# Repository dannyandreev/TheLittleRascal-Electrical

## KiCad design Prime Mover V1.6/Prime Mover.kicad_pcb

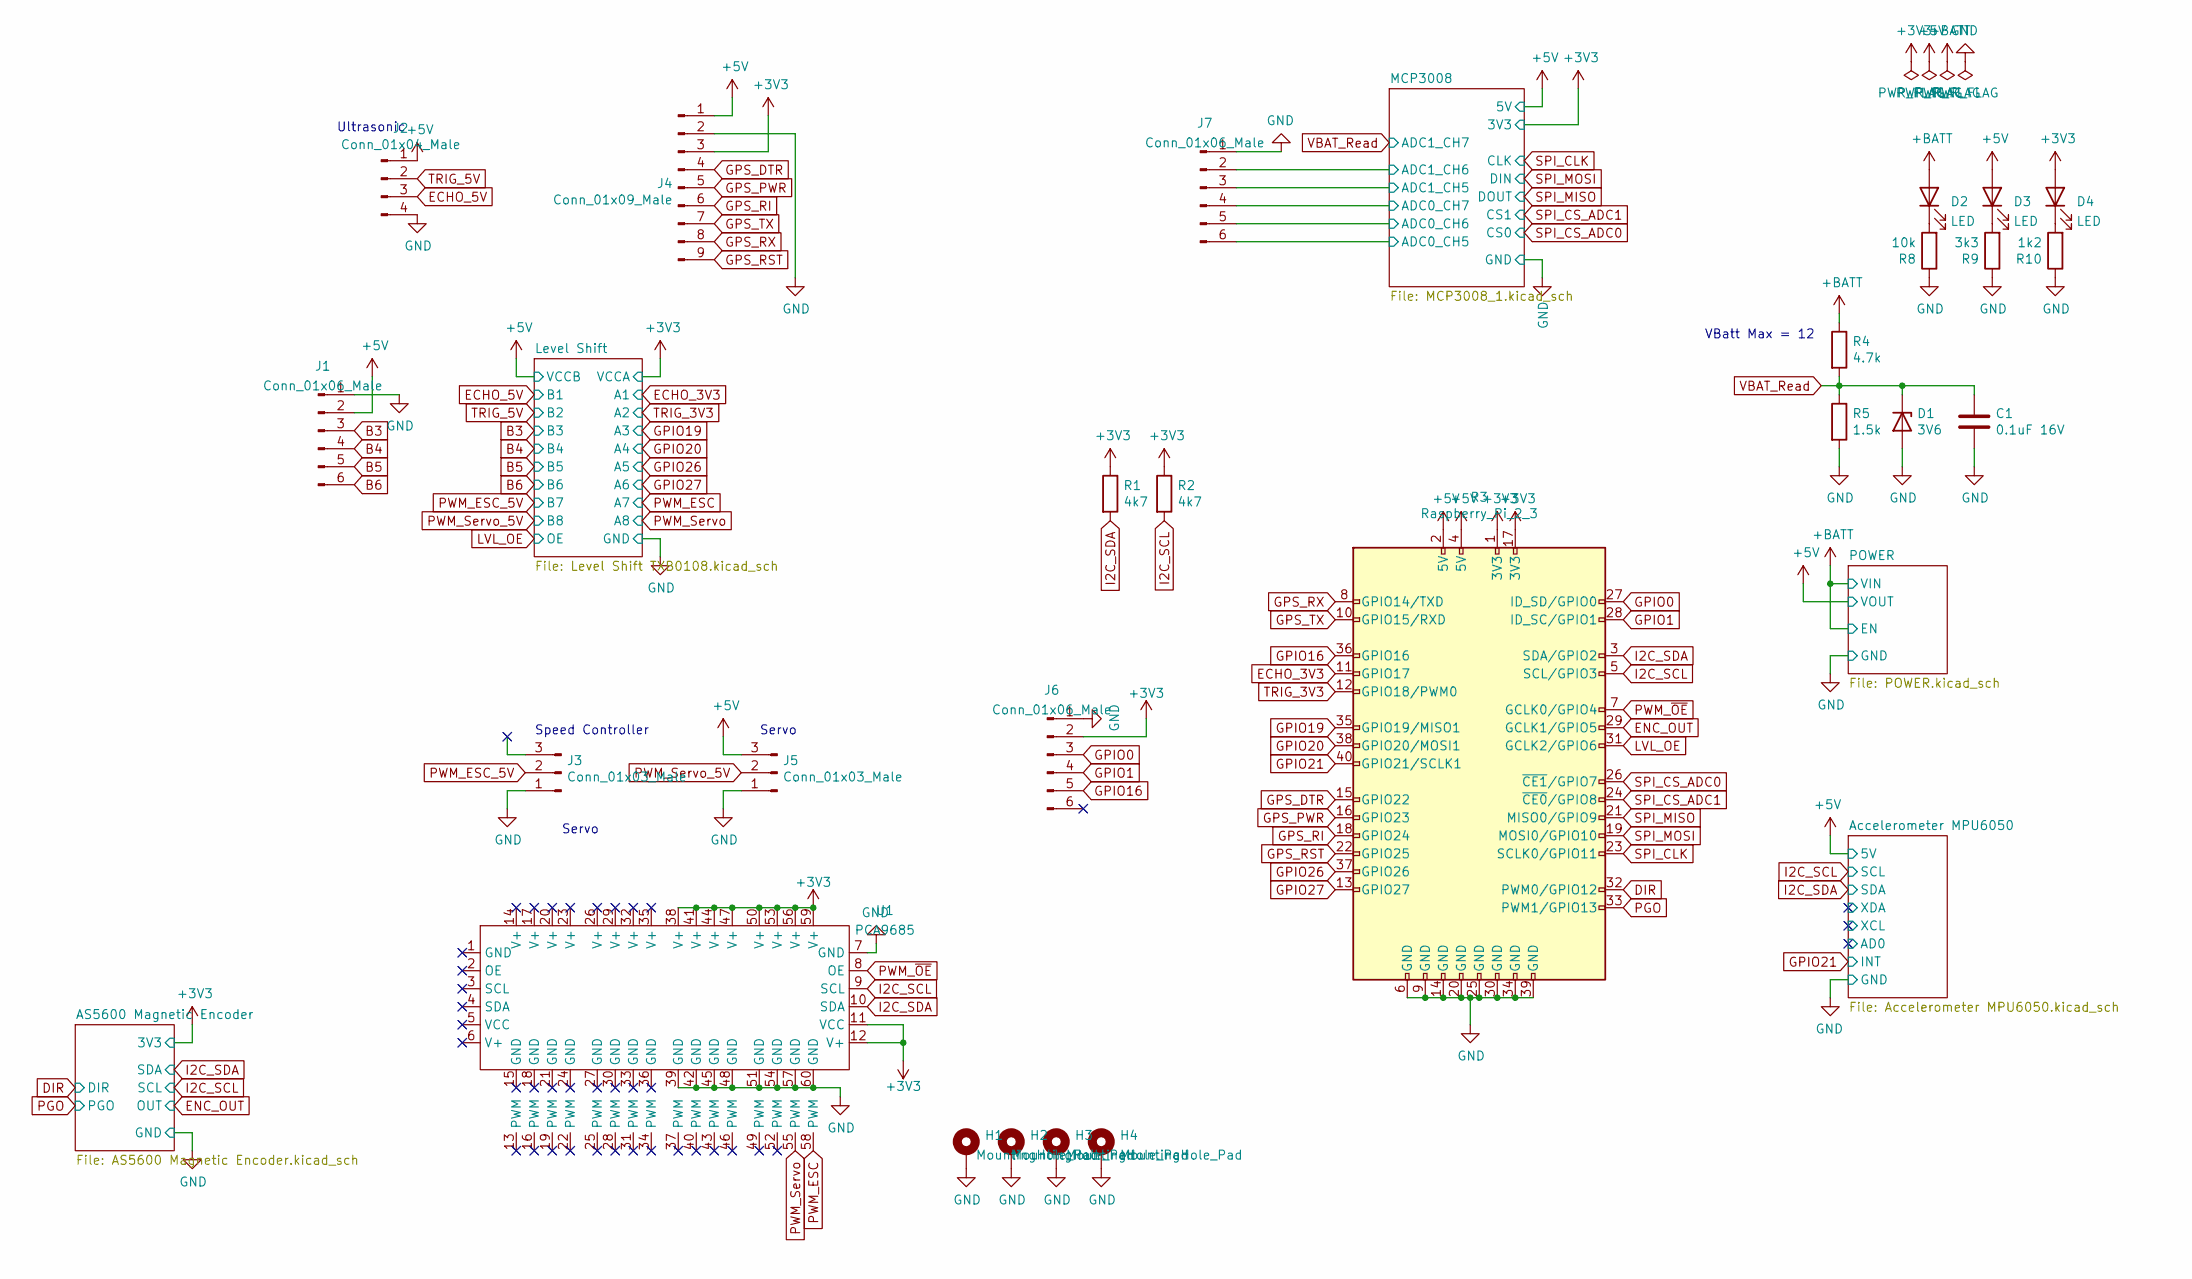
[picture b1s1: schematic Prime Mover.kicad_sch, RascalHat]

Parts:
C1: 0.1uF 16V; C_0805_2012Metric
D1: 3V6; D_SOD-323_HandSoldering
D2, D3, D4: LED; LED_0805_2012Metric
H1, H2, H3, H4: MountingHole_Pad; MountingHole_3.2mm_M3_DIN965_Pad
J1, J6, J7: Conn_01x06_Male; JST_PH_B6B-PH-K_1x06_P2.00mm_Vertical
J2: Conn_01x04_Male; JST_PH_B4B-PH-K_1x04_P2.00mm_Vertical
J3, J5: Conn_01x03_Male; JST_PH_B3B-PH-K_1x03_P2.00mm_Vertical
J4: Conn_01x09_Male; JST_PH_B9B-PH-K_1x09_P2.00mm_Vertical
R1, R2: 4k7; R_0805_2012Metric
R3: Raspberry_Pi_2_3; PinSocket_2x20_P2.54mm_Vertical
R4: 4.7k; R_0805_2012Metric
R5: 1.5k; R_0805_2012Metric
R8: 10k; R_0805_2012Metric
R9: 3k3; R_0805_2012Metric
R10: 1k2; R_0805_2012Metric
U1: PCA9685; PCA9685 HW170

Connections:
+3V3: D4.2 (A), J4.3, J6.2, R1.1, R2.1, R3.1 (3V3), R3.17 (3V3), U1.11 (VCC), U1.12 (V+), U1.38 (V+), U1.41 (V+), U1.44 (V+), U1.47 (V+), U1.50 (V+), U1.53 (V+), U1.56 (V+), U1.59 (V+); also elsewhere on the board
+5V: D3.2 (A), J1.2, J2.1, J4.1, J5.3, R3.2 (5V), R3.4 (5V); also elsewhere on the board
+BATT: D2.2 (A), R4.1; also elsewhere on the board
/MCP3008/ADC0_CH5: J7.6; also elsewhere on the board
/MCP3008/ADC0_CH6: J7.5; also elsewhere on the board
/MCP3008/ADC0_CH7: J7.4; also elsewhere on the board
/MCP3008/ADC1_CH5: J7.3; also elsewhere on the board
/MCP3008/ADC1_CH6: J7.2; also elsewhere on the board
B3: J1.3; also elsewhere on the board
B4: J1.4; also elsewhere on the board
B5: J1.5; also elsewhere on the board
B6: J1.6; also elsewhere on the board
DIR: R3.32 (PWM0/GPIO12); also elsewhere on the board
ECHO_3V3: R3.11 (GPIO17); also elsewhere on the board
ECHO_5V: J2.3; also elsewhere on the board
ENC_OUT: R3.29 (GCLK1/GPIO5); also elsewhere on the board
GND: C1.2, D1.2 (A), H1.1, H2.1, H3.1, H4.1, J1.1, J2.4, J3.1, J4.2, J5.1, J6.1, J7.1, R3.6 (GND), R3.9 (GND), R3.14 (GND), R3.20 (GND), R3.25 (GND), R3.30 (GND), R3.34 (GND), R3.39 (GND), R5.2, R8.1, R9.1, R10.1, U1.7 (GND), U1.39 (GND), U1.42 (GND), U1.45 (GND), U1.48 (GND), U1.51 (GND), U1.54 (GND), U1.57 (GND), U1.60 (GND); also elsewhere on the board
GPIO0: J6.3, R3.27 (ID_SD/GPIO0)
GPIO1: J6.4, R3.28 (ID_SC/GPIO1)
GPIO16: J6.5, R3.36 (GPIO16)
GPIO19: R3.35 (GPIO19/MISO1); also elsewhere on the board
GPIO20: R3.38 (GPIO20/MOSI1); also elsewhere on the board
GPIO21: R3.40 (GPIO21/SCLK1); also elsewhere on the board
GPIO26: R3.37 (GPIO26); also elsewhere on the board
GPIO27: R3.13 (GPIO27); also elsewhere on the board
GPS_DTR: J4.4, R3.15 (GPIO22)
GPS_PWR: J4.5, R3.16 (GPIO23)
GPS_RI: J4.6, R3.18 (GPIO24)
GPS_RST: J4.9, R3.22 (GPIO25)
GPS_RX: J4.8, R3.8 (GPIO14/TXD)
GPS_TX: J4.7, R3.10 (GPIO15/RXD)
I2C_SCL: R2.2, R3.5 (SCL/GPIO3), U1.9 (SCL); also elsewhere on the board
I2C_SDA: R1.2, R3.3 (SDA/GPIO2), U1.10 (SDA); also elsewhere on the board
LVL_OE: R3.31 (GCLK2/GPIO6); also elsewhere on the board
unnamed: D2.1 (K), R8.2
unnamed: D3.1 (K), R9.2
unnamed: D4.1 (K), R10.2
PGO: R3.33 (PWM1/GPIO13); also elsewhere on the board
PWM_ESC: U1.58 (PWM); also elsewhere on the board
PWM_ESC_5V: J3.2; also elsewhere on the board
PWM_Servo: U1.55 (PWM); also elsewhere on the board
PWM_Servo_5V: J5.2; also elsewhere on the board
PWM_~OE: R3.7 (GCLK0/GPIO4), U1.8 (OE)
SPI_CLK: R3.23 (SCLK0/GPIO11); also elsewhere on the board
SPI_CS_ADC0: R3.26 (~CE1/GPIO7); also elsewhere on the board
SPI_CS_ADC1: R3.24 (~CE0/GPIO8); also elsewhere on the board
SPI_MISO: R3.21 (MISO0/GPIO9); also elsewhere on the board
SPI_MOSI: R3.19 (MOSI0/GPIO10); also elsewhere on the board
TRIG_3V3: R3.12 (GPIO18/PWM0); also elsewhere on the board
TRIG_5V: J2.2; also elsewhere on the board
VBAT_Read: C1.1, D1.1 (K), R4.2, R5.1; also elsewhere on the board

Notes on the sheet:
Servo
VBatt Max = 12
Ultrasonic
Speed Controller

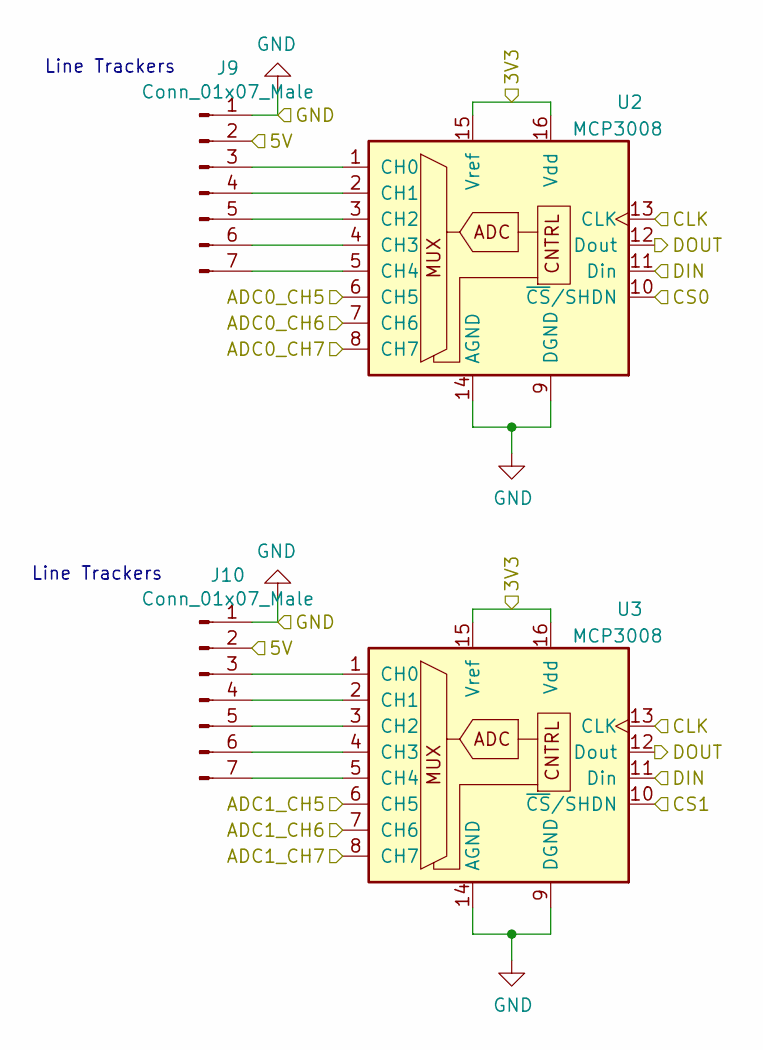
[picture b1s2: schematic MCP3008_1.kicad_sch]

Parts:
J9, J10: Conn_01x07_Male; JST_PH_B7B-PH-K_1x07_P2.00mm_Vertical
U2, U3: MCP3008; SOIC-16_3.9x9.9mm_P1.27mm

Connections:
+3V3: U2.15 (Vref), U2.16 (Vdd), U3.15 (Vref), U3.16 (Vdd); also elsewhere on the board
+5V: J9.2, J10.2; also elsewhere on the board
/MCP3008/ADC0_CH5: U2.6 (CH5); also elsewhere on the board
/MCP3008/ADC0_CH6: U2.7 (CH6); also elsewhere on the board
/MCP3008/ADC0_CH7: U2.8 (CH7); also elsewhere on the board
/MCP3008/ADC1_CH5: U3.6 (CH5); also elsewhere on the board
/MCP3008/ADC1_CH6: U3.7 (CH6); also elsewhere on the board
GND: J9.1, J10.1, U2.9 (DGND), U2.14 (AGND), U3.9 (DGND), U3.14 (AGND); also elsewhere on the board
unnamed: J9.3, U2.1 (CH0)
unnamed: J9.4, U2.2 (CH1)
unnamed: J9.5, U2.3 (CH2)
unnamed: J9.6, U2.4 (CH3)
unnamed: J9.7, U2.5 (CH4)
unnamed: J10.3, U3.1 (CH0)
unnamed: J10.4, U3.2 (CH1)
unnamed: J10.5, U3.3 (CH2)
unnamed: J10.6, U3.4 (CH3)
unnamed: J10.7, U3.5 (CH4)
SPI_CLK: U2.13 (CLK), U3.13 (CLK); also elsewhere on the board
SPI_CS_ADC0: U2.10 (~CS/SHDN); also elsewhere on the board
SPI_CS_ADC1: U3.10 (~CS/SHDN); also elsewhere on the board
SPI_MISO: U2.12 (Dout), U3.12 (Dout); also elsewhere on the board
SPI_MOSI: U2.11 (Din), U3.11 (Din); also elsewhere on the board
VBAT_Read: U3.8 (CH7); also elsewhere on the board

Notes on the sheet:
Line Trackers

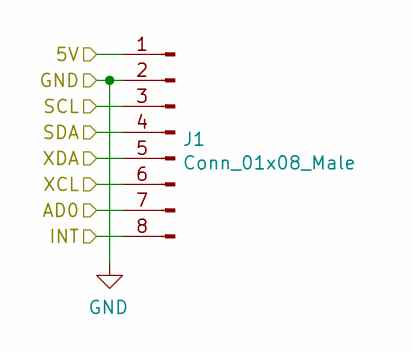
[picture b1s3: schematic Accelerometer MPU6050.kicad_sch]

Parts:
J1: Conn_01x08_Male; MPU-6050-Module

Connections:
+5V: J1.2; also elsewhere on the board
B3: J1.3; also elsewhere on the board
B4: J1.4; also elsewhere on the board
B5: J1.5; also elsewhere on the board
B6: J1.6; also elsewhere on the board
GND: J1.1; also elsewhere on the board

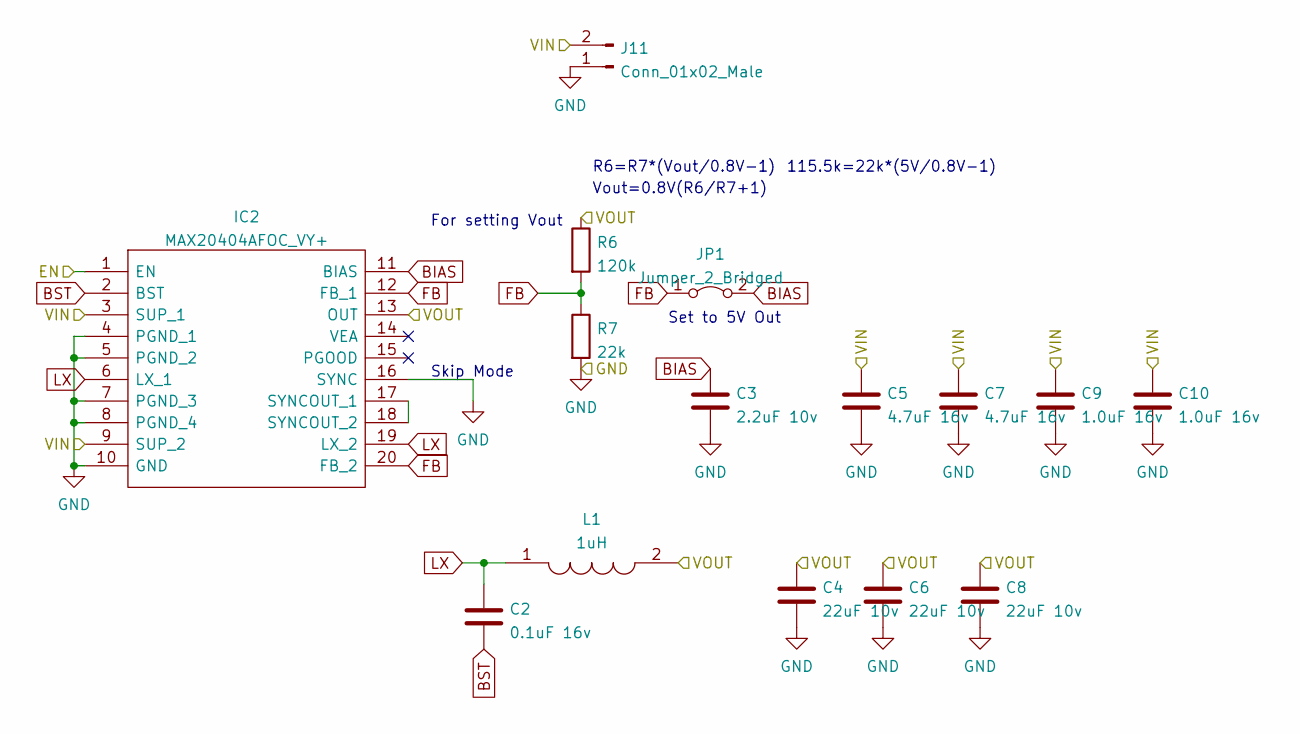
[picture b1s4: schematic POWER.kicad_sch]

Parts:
C2: 0.1uF 16v; C_0805_2012Metric
C3: 2.2uF 10v; C_0805_2012Metric
C4, C6, C8: 22uF 10v; CP_Elec_5x5.3
C5, C7: 4.7uF 16v; C_0805_2012Metric
C9, C10: 1.0uF 16v; C_0805_2012Metric
IC2: MAX20404AFOC_VY+; MAX20404AFOCVY; Manufacturer_Part_Number MAX20404AFOC/VY+
J11: Conn_01x02_Male; AMASS_XT60-M_1x02_P7.20mm_Vertical
JP1: Jumper_2_Bridged; SolderJumper-2_P1.3mm_Open_RoundedPad1.0x1.5mm
L1: 1uH; INDPM7066X500N; Manufacturer_Part_Number MWSA0605S-150MT
R6: 120k; R_0805_2012Metric
R7: 22k; R_0805_2012Metric

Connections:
+5V: C4.1, C6.1, C8.1, IC2.13 (OUT), L1.2, R6.1; also elsewhere on the board
+BATT: C5.1, C7.1, C9.1, C10.1, IC2.1 (EN), IC2.3 (SUP_1), IC2.9 (SUP_2), J11.2; also elsewhere on the board
BIAS: C3.1, IC2.11 (BIAS), JP1.2 (B)
BST: C2.2, IC2.2 (BST)
FB: IC2.12 (FB_1), IC2.20 (FB_2), JP1.1 (A), R6.2, R7.1
GND: C3.2, C4.2, C5.2, C6.2, C7.2, C8.2, C9.2, C10.2, IC2.4 (PGND_1), IC2.5 (PGND_2), IC2.7 (PGND_3), IC2.8 (PGND_4), IC2.10 (GND), IC2.16 (SYNC), J11.1, R7.2; also elsewhere on the board
LX: C2.1, IC2.6 (LX_1), IC2.19 (LX_2), L1.1
unnamed: IC2.17 (SYNCOUT_1), IC2.18 (SYNCOUT_2)

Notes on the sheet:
Vout=0.8V(R6/R7+1)
For setting Vout
Skip Mode
Set to 5V Out
R6=R7*(Vout/0.8V-1)
115.5k=22k*(5V/0.8V-1)

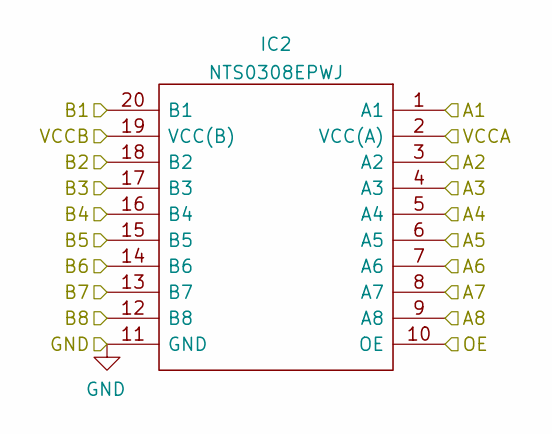
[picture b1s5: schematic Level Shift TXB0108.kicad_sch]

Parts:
IC2: NTS0308EPWJ; SOP65P640X110-20N; Manufacturer_Part_Number NTS0308EPWJ; Mouser Part Number 771-NTS0308EPWJ

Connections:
+5V: IC2.13 (OUT); also elsewhere on the board
+BATT: IC2.1 (EN), IC2.3 (SUP_1), IC2.9 (SUP_2); also elsewhere on the board
BIAS: IC2.11 (BIAS); also elsewhere on the board
BST: IC2.2 (BST); also elsewhere on the board
FB: IC2.12 (FB_1), IC2.20 (FB_2); also elsewhere on the board
GND: IC2.4 (PGND_1), IC2.5 (PGND_2), IC2.7 (PGND_3), IC2.8 (PGND_4), IC2.10 (GND), IC2.16 (SYNC); also elsewhere on the board
LX: IC2.6 (LX_1), IC2.19 (LX_2); also elsewhere on the board
unnamed: IC2.17 (SYNCOUT_1), IC2.18 (SYNCOUT_2)

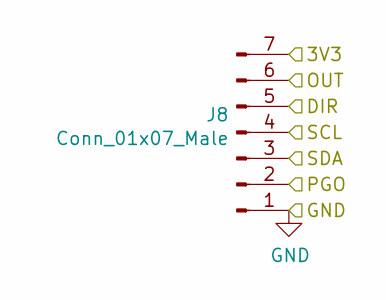
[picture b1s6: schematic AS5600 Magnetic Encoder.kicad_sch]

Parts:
J8: Conn_01x07_Male; JST_PH_B7B-PH-K_1x07_P2.00mm_Vertical

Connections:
+3V3: J8.7; also elsewhere on the board
DIR: J8.5; also elsewhere on the board
ENC_OUT: J8.6; also elsewhere on the board
GND: J8.1; also elsewhere on the board
I2C_SCL: J8.4; also elsewhere on the board
I2C_SDA: J8.3; also elsewhere on the board
PGO: J8.2; also elsewhere on the board

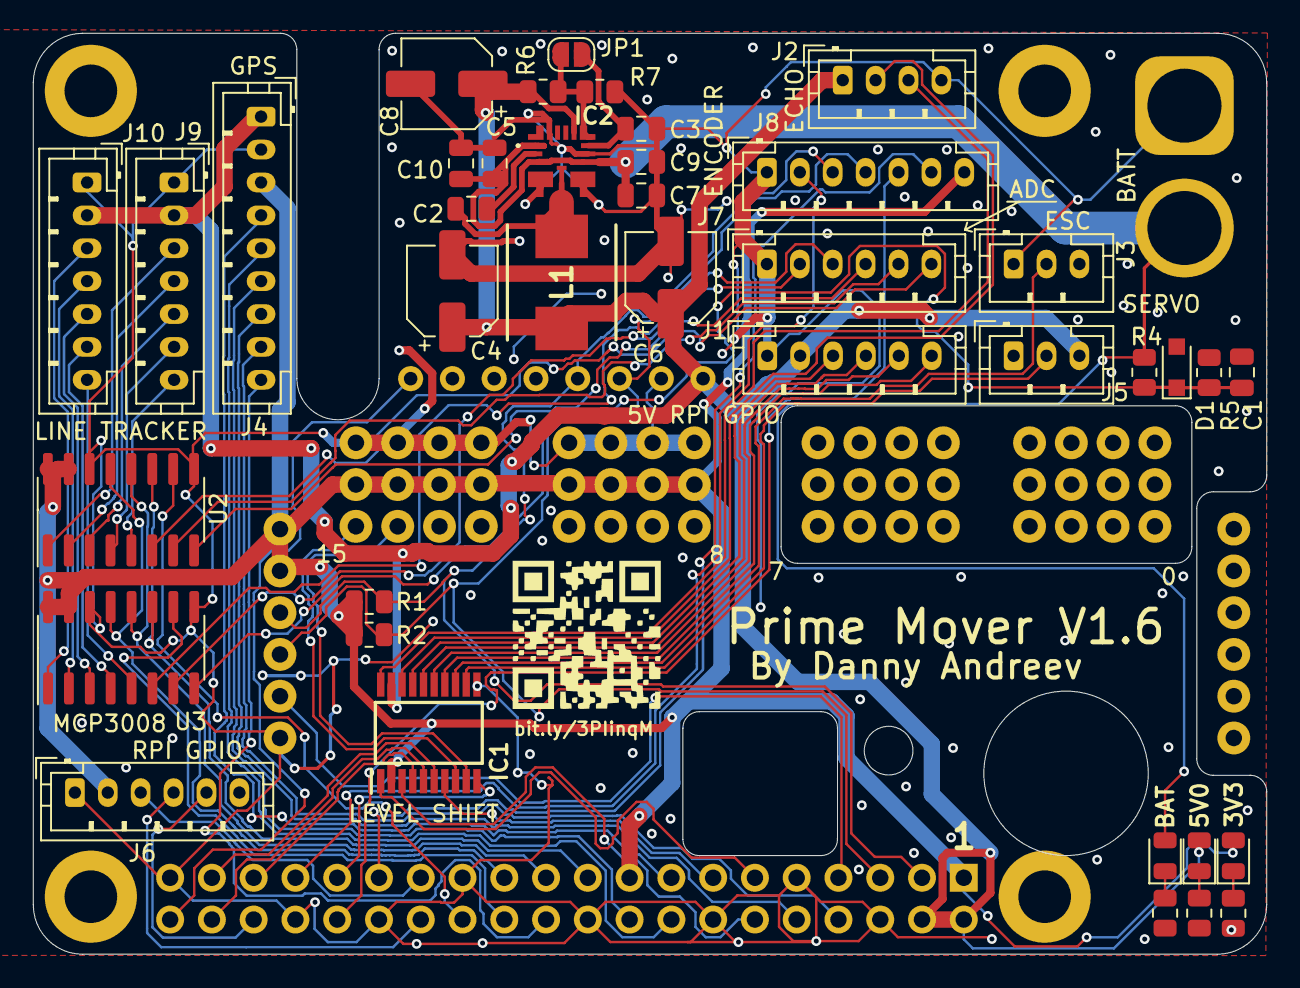
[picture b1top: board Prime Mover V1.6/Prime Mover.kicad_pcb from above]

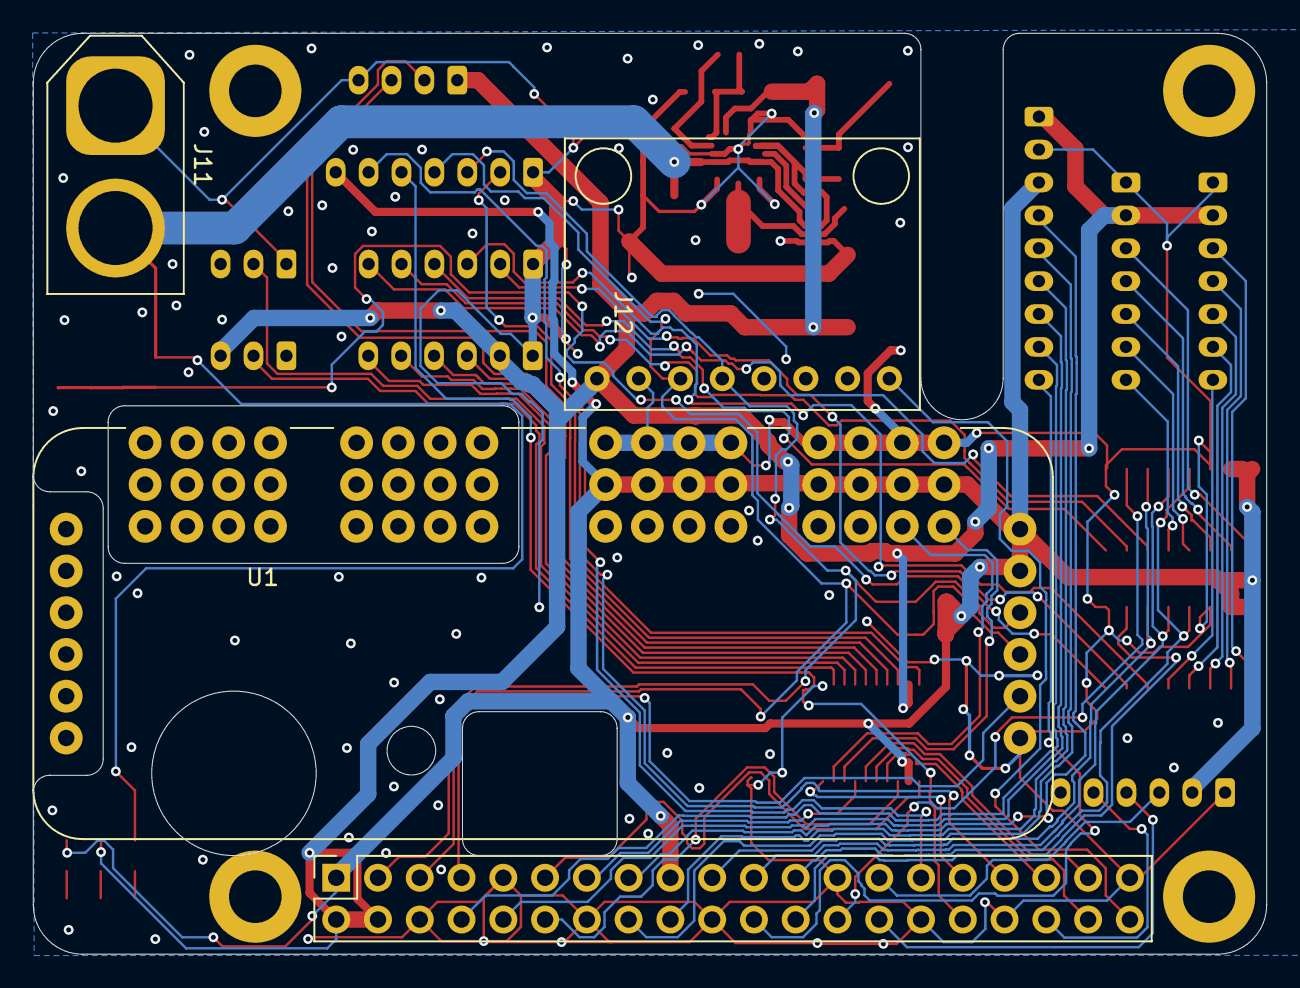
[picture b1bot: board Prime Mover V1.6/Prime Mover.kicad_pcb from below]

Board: 2 copper layers, 75.0 x 56.0 mm, 47 parts (3 on the bottom side), 66 nets.

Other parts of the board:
IC1: NTS0308EPWJ; SOP65P640X110-20N
J12: Conn_01x08_Male; MPU-6050-Module

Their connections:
+3V3: IC1.2 (VCC(A)); also elsewhere on the board
+5V: IC1.19 (VCC(B)), J12.1; also elsewhere on the board
B3: IC1.17 (B3); also elsewhere on the board
B4: IC1.16 (B4); also elsewhere on the board
B5: IC1.15 (B5); also elsewhere on the board
B6: IC1.14 (B6); also elsewhere on the board
ECHO_3V3: IC1.1 (A1); also elsewhere on the board
ECHO_5V: IC1.20 (B1); also elsewhere on the board
GND: IC1.11 (GND), J12.2; also elsewhere on the board
GPIO19: IC1.4 (A3); also elsewhere on the board
GPIO20: IC1.5 (A4); also elsewhere on the board
GPIO21: J12.8; also elsewhere on the board
GPIO26: IC1.6 (A5); also elsewhere on the board
GPIO27: IC1.7 (A6); also elsewhere on the board
I2C_SCL: J12.3; also elsewhere on the board
I2C_SDA: J12.4; also elsewhere on the board
LVL_OE: IC1.10 (OE); also elsewhere on the board
PWM_ESC: IC1.8 (A7); also elsewhere on the board
PWM_ESC_5V: IC1.13 (B7); also elsewhere on the board
PWM_Servo: IC1.9 (A8); also elsewhere on the board
PWM_Servo_5V: IC1.12 (B8); also elsewhere on the board
TRIG_3V3: IC1.3 (A2); also elsewhere on the board
TRIG_5V: IC1.18 (B2); also elsewhere on the board

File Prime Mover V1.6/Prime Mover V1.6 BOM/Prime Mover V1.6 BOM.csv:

Id,Designator,Package,Quantity,Designation,Supplier and ref,
1,JP1,SolderJumper-2_P1.3mm_Open_RoundedPad1.0x1.5mm,1,Jumper_2_Bridged,N/A,
2,"C7,C5",C_0805_2012Metric,2,4.7uF 16v,EMF212AB7475MGHT ,
3,"J7,J6,J1",JST_PH_B6B-PH-K_1x06_P2.00mm_Vertical,3,Conn_01x06_Male,B6B-PH-K-S(LF)(SN) ,
4,"C8,C6,C4",CP_Elec_5x5.3,3,22uF 10v,875105242005,Double Check
5,IC1,SOP65P640X110-20N,1,NTS0308EPWJ,NTS0308EPWJ,
6,"U2,U3",SOIC-16_3.9x9.9mm_P1.27mm,2,MCP3008,MCP3008,
7,"J9,J10,J8",JST_PH_B7B-PH-K_1x07_P2.00mm_Vertical,3,Conn_01x07_Male,B7B-PH-K-S(LF)(SN),
8,"H1,H4,H3,H2",MountingHole_3.2mm_M3_DIN965_Pad,4,MountingHole_Pad,N/A,
9,R8,R_0805_2012Metric,1,10k,RMCF0805JT10K0 ,
10,"D2,D4,D3",LED_0805_2012Metric,3,LED,XZMOK54W-1 ,
11,R6,R_0805_2012Metric,1,120k,RMCF0805JT120K ,
12,L1,INDPM7066X500N,1,1uH,MWSA0624S-1R0MT ,
13,J2,JST_PH_B4B-PH-K_1x04_P2.00mm_Vertical,1,Conn_01x04_Male,B4B-PH-K-S(LF)(SN) ,
14,R7,R_0805_2012Metric,1,22k,ERJ-6GEYJ223V ,
15,"C10,C9",C_0805_2012Metric,2,1.0uF 16v,CC0805MKX7R7BB105 ,
16,J4,JST_PH_B9B-PH-K_1x09_P2.00mm_Vertical,1,Conn_01x09_Male,B9B-PH-K-S(LF)(SN) ,
17,R10,R_0805_2012Metric,1,1k2,RMCF0805JT1K20 ,
18,U1,PCA9685 HW170,0,PCA9685,N/A,
19,"R2,R1",R_0805_2012Metric,2,4k7,RMCF0805JT4K70 ,
20,R4,R_0805_2012Metric,1,4.7k,RMCF0805JT4K70 ,
21,R9,R_0805_2012Metric,1,3k3,RNCF0805DTE3K32 ,
22,"J3,J5",JST_PH_B3B-PH-K_1x03_P2.00mm_Vertical,2,Conn_01x03_Male,B3B-PH-K-S(LF)(SN) ,
23,IC2,MAX20404AFOCVY,1,MAX20404AFOC_VY+,MAX20405AFOD/VY+ ,
24,R5,R_0805_2012Metric,1,1.5k,RNCP0805FTD1K50 ,
25,C1,C_0805_2012Metric,1,0.1uF 16V,0805YC104JAT4A ,
26,D1,D_SOD-323_HandSoldering,1,3V6,BZT52C3V6S-7-F ,
27,C2,C_0805_2012Metric,1,0.1uF 16v,0805YC104JAT4A ,
28,C3,C_0805_2012Metric,1,2.2uF 10v,C0805X225K8RAC7800 ,
29,J11,AMASS_XT60-M_1x02_P7.20mm_Vertical,1,Conn_01x02_Male,AMASS_XT60-M,
30,R3,PinSocket_2x20_P2.54mm_Vertical,1,Raspberry_Pi_2_3,PPTC202LFBN-RC ,
31,J12,MPU-6050-Module,0,Conn_01x08_Male,N/A,

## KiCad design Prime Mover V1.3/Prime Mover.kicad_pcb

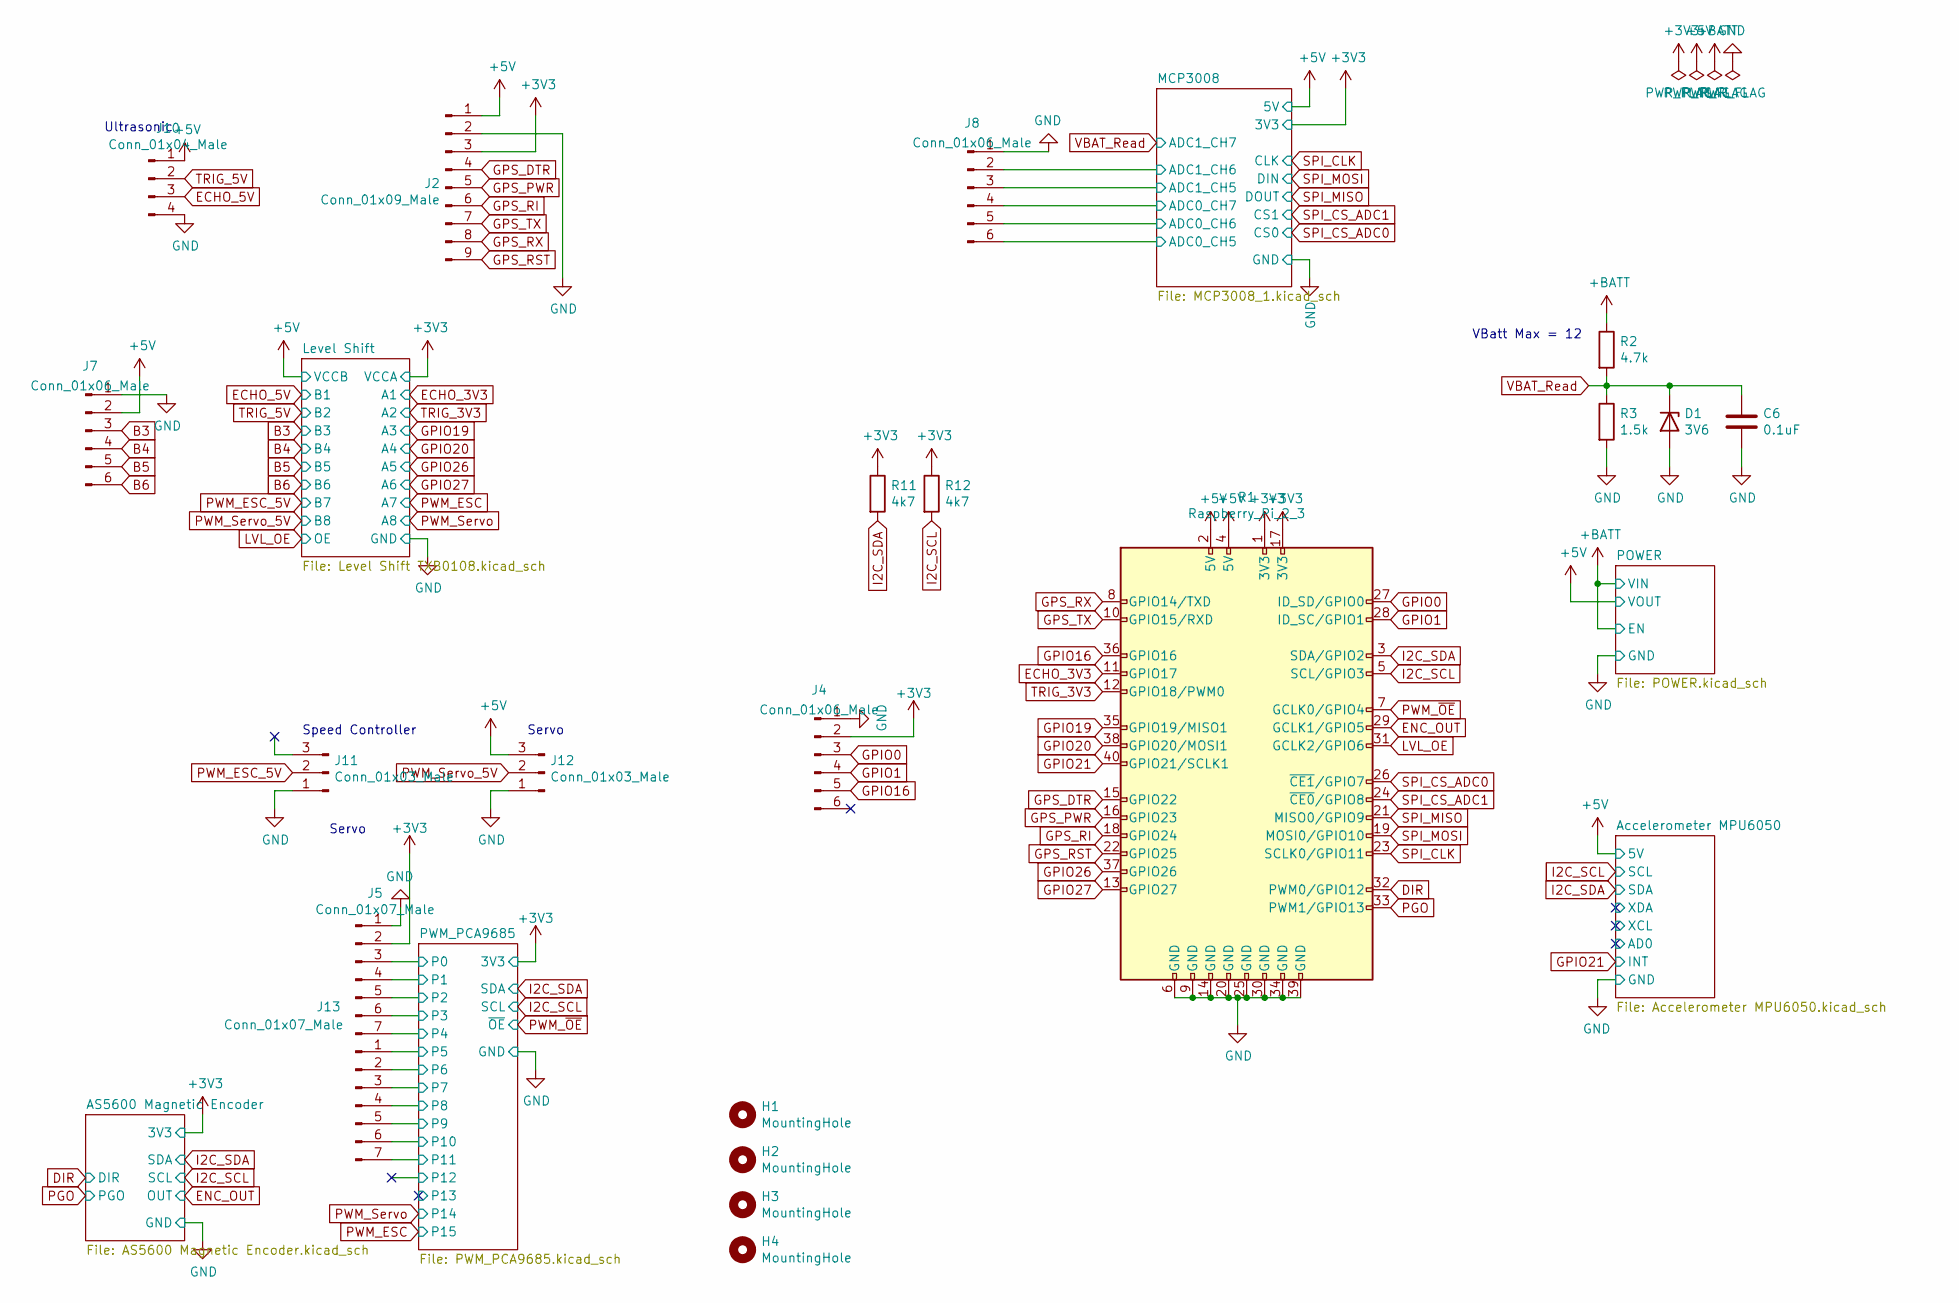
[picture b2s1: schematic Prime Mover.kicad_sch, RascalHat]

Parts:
C6: 0.1uF; C_0805_2012Metric
D1: 3V6; D_SOD-323_HandSoldering
H1, H2, H3, H4: MountingHole; MountingHole_3.2mm_M3
J2: Conn_01x09_Male; JST_PH_B9B-PH-K_1x09_P2.00mm_Vertical
J4, J7, J8: Conn_01x06_Male; JST_PH_B6B-PH-K_1x06_P2.00mm_Vertical
J5, J13: Conn_01x07_Male; JST_PH_B7B-PH-K_1x07_P2.00mm_Vertical
J10: Conn_01x04_Male; JST_PH_B4B-PH-K_1x04_P2.00mm_Vertical
J11, J12: Conn_01x03_Male; JST_PH_B3B-PH-K_1x03_P2.00mm_Vertical
R1: Raspberry_Pi_2_3; PinSocket_2x20_P2.54mm_Vertical
R2: 4.7k; R_0805_2012Metric
R3: 1.5k; R_0805_2012Metric
R11, R12: 4k7; R_0805_2012Metric

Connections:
+3V3: J2.3, J4.2, J5.2, R1.1 (3V3), R1.17 (3V3), R11.1, R12.1; also elsewhere on the board
+5V: J2.1, J7.2, J10.1, J12.3, R1.2 (5V), R1.4 (5V); also elsewhere on the board
+BATT: R2.1; also elsewhere on the board
/MCP3008/ADC0_CH5: J8.6; also elsewhere on the board
/MCP3008/ADC0_CH6: J8.5; also elsewhere on the board
/MCP3008/ADC0_CH7: J8.4; also elsewhere on the board
/MCP3008/ADC1_CH5: J8.3; also elsewhere on the board
/MCP3008/ADC1_CH6: J8.2; also elsewhere on the board
/PWM_PCA9685/P0: J5.3; also elsewhere on the board
/PWM_PCA9685/P1: J5.4; also elsewhere on the board
/PWM_PCA9685/P2: J5.5; also elsewhere on the board
/PWM_PCA9685/P3: J5.6; also elsewhere on the board
/PWM_PCA9685/P4: J5.7; also elsewhere on the board
/PWM_PCA9685/P5: J13.1; also elsewhere on the board
/PWM_PCA9685/P6: J13.2; also elsewhere on the board
/PWM_PCA9685/P7: J13.3; also elsewhere on the board
/PWM_PCA9685/P8: J13.4; also elsewhere on the board
/PWM_PCA9685/P9: J13.5; also elsewhere on the board
/PWM_PCA9685/P10: J13.6; also elsewhere on the board
/PWM_PCA9685/P11: J13.7; also elsewhere on the board
B3: J7.3; also elsewhere on the board
B4: J7.4; also elsewhere on the board
B5: J7.5; also elsewhere on the board
B6: J7.6; also elsewhere on the board
DIR: R1.32 (PWM0/GPIO12); also elsewhere on the board
ECHO_3V3: R1.11 (GPIO17); also elsewhere on the board
ECHO_5V: J10.3; also elsewhere on the board
ENC_OUT: R1.29 (GCLK1/GPIO5); also elsewhere on the board
GND: C6.2, D1.2 (A), J2.2, J4.1, J5.1, J7.1, J8.1, J10.4, J11.1, J12.1, R1.6 (GND), R1.9 (GND), R1.14 (GND), R1.20 (GND), R1.25 (GND), R1.30 (GND), R1.34 (GND), R1.39 (GND), R3.2; also elsewhere on the board
GPIO0: J4.3, R1.27 (ID_SD/GPIO0)
GPIO1: J4.4, R1.28 (ID_SC/GPIO1)
GPIO16: J4.5, R1.36 (GPIO16)
GPIO19: R1.35 (GPIO19/MISO1); also elsewhere on the board
GPIO20: R1.38 (GPIO20/MOSI1); also elsewhere on the board
GPIO21: R1.40 (GPIO21/SCLK1); also elsewhere on the board
GPIO26: R1.37 (GPIO26); also elsewhere on the board
GPIO27: R1.13 (GPIO27); also elsewhere on the board
GPS_DTR: J2.4, R1.15 (GPIO22)
GPS_PWR: J2.5, R1.16 (GPIO23)
GPS_RI: J2.6, R1.18 (GPIO24)
GPS_RST: J2.9, R1.22 (GPIO25)
GPS_RX: J2.8, R1.8 (GPIO14/TXD)
GPS_TX: J2.7, R1.10 (GPIO15/RXD)
I2C_SCL: R1.5 (SCL/GPIO3), R12.2; also elsewhere on the board
I2C_SDA: R1.3 (SDA/GPIO2), R11.2; also elsewhere on the board
LVL_OE: R1.31 (GCLK2/GPIO6); also elsewhere on the board
PGO: R1.33 (PWM1/GPIO13); also elsewhere on the board
PWM_ESC_5V: J11.2; also elsewhere on the board
PWM_Servo_5V: J12.2; also elsewhere on the board
PWM_~OE: R1.7 (GCLK0/GPIO4); also elsewhere on the board
SPI_CLK: R1.23 (SCLK0/GPIO11); also elsewhere on the board
SPI_CS_ADC0: R1.26 (~CE1/GPIO7); also elsewhere on the board
SPI_CS_ADC1: R1.24 (~CE0/GPIO8); also elsewhere on the board
SPI_MISO: R1.21 (MISO0/GPIO9); also elsewhere on the board
SPI_MOSI: R1.19 (MOSI0/GPIO10); also elsewhere on the board
TRIG_3V3: R1.12 (GPIO18/PWM0); also elsewhere on the board
TRIG_5V: J10.2; also elsewhere on the board
VBAT_Read: C6.1, D1.1 (K), R2.2, R3.1; also elsewhere on the board

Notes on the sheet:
Servo
VBatt Max = 12
Ultrasonic
Speed Controller

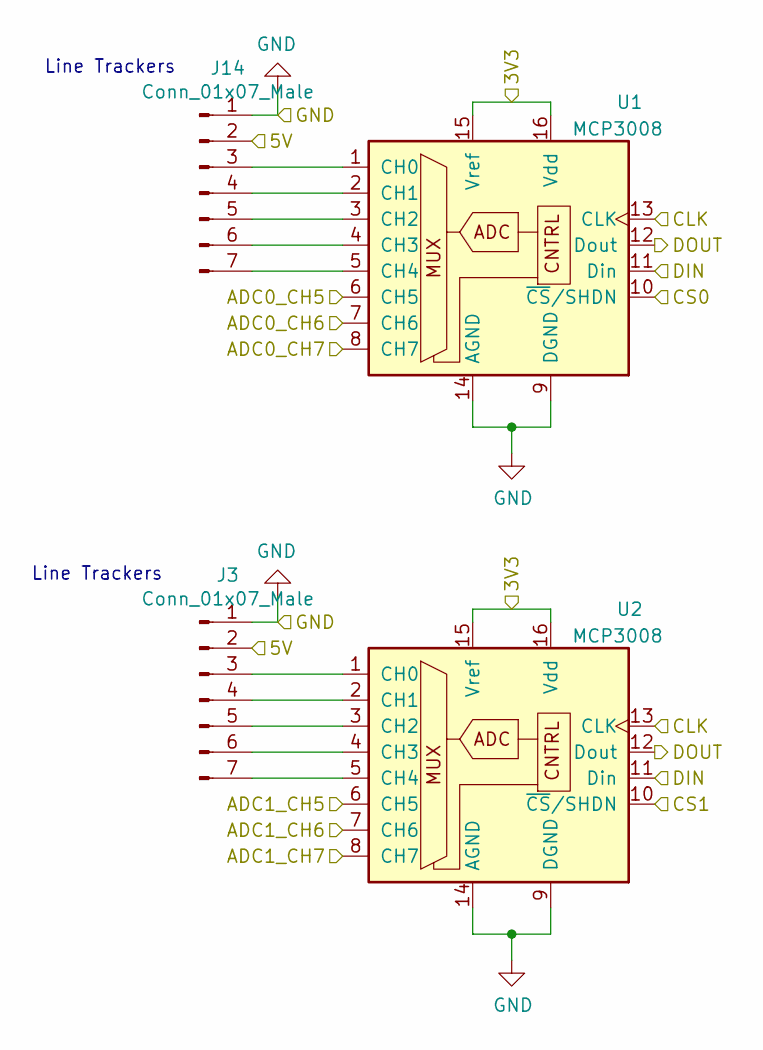
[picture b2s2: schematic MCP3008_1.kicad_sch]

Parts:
J3, J14: Conn_01x07_Male; JST_PH_B7B-PH-K_1x07_P2.00mm_Vertical
U1, U2: MCP3008; SOIC-16_3.9x9.9mm_P1.27mm

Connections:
+3V3: U1.15 (Vref), U1.16 (Vdd), U2.15 (Vref), U2.16 (Vdd); also elsewhere on the board
+5V: J3.2, J14.2; also elsewhere on the board
/MCP3008/ADC0_CH5: U1.6 (CH5); also elsewhere on the board
/MCP3008/ADC0_CH6: U1.7 (CH6); also elsewhere on the board
/MCP3008/ADC0_CH7: U1.8 (CH7); also elsewhere on the board
/MCP3008/ADC1_CH5: U2.6 (CH5); also elsewhere on the board
/MCP3008/ADC1_CH6: U2.7 (CH6); also elsewhere on the board
GND: J3.1, J14.1, U1.9 (DGND), U1.14 (AGND), U2.9 (DGND), U2.14 (AGND); also elsewhere on the board
unnamed: J3.3, U2.1 (CH0)
unnamed: J3.4, U2.2 (CH1)
unnamed: J3.5, U2.3 (CH2)
unnamed: J3.6, U2.4 (CH3)
unnamed: J3.7, U2.5 (CH4)
unnamed: J14.3, U1.1 (CH0)
unnamed: J14.4, U1.2 (CH1)
unnamed: J14.5, U1.3 (CH2)
unnamed: J14.6, U1.4 (CH3)
unnamed: J14.7, U1.5 (CH4)
SPI_CLK: U1.13 (CLK), U2.13 (CLK); also elsewhere on the board
SPI_CS_ADC0: U1.10 (~CS/SHDN); also elsewhere on the board
SPI_CS_ADC1: U2.10 (~CS/SHDN); also elsewhere on the board
SPI_MISO: U1.12 (Dout), U2.12 (Dout); also elsewhere on the board
SPI_MOSI: U1.11 (Din), U2.11 (Din); also elsewhere on the board
VBAT_Read: U2.8 (CH7); also elsewhere on the board

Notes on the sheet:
Line Trackers

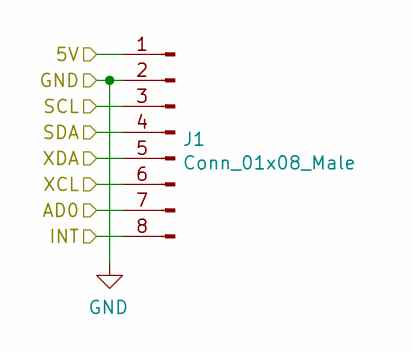
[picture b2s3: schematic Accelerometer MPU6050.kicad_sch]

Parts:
J1: Conn_01x08_Male; MPU-6050-Module

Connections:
+5V: J1.1; also elsewhere on the board
/Accelerometer MPU6050/AD0: J1.7
/Accelerometer MPU6050/XCL: J1.6
/Accelerometer MPU6050/XDA: J1.5
GND: J1.2; also elsewhere on the board
GPIO21: J1.8; also elsewhere on the board
I2C_SCL: J1.3; also elsewhere on the board
I2C_SDA: J1.4; also elsewhere on the board

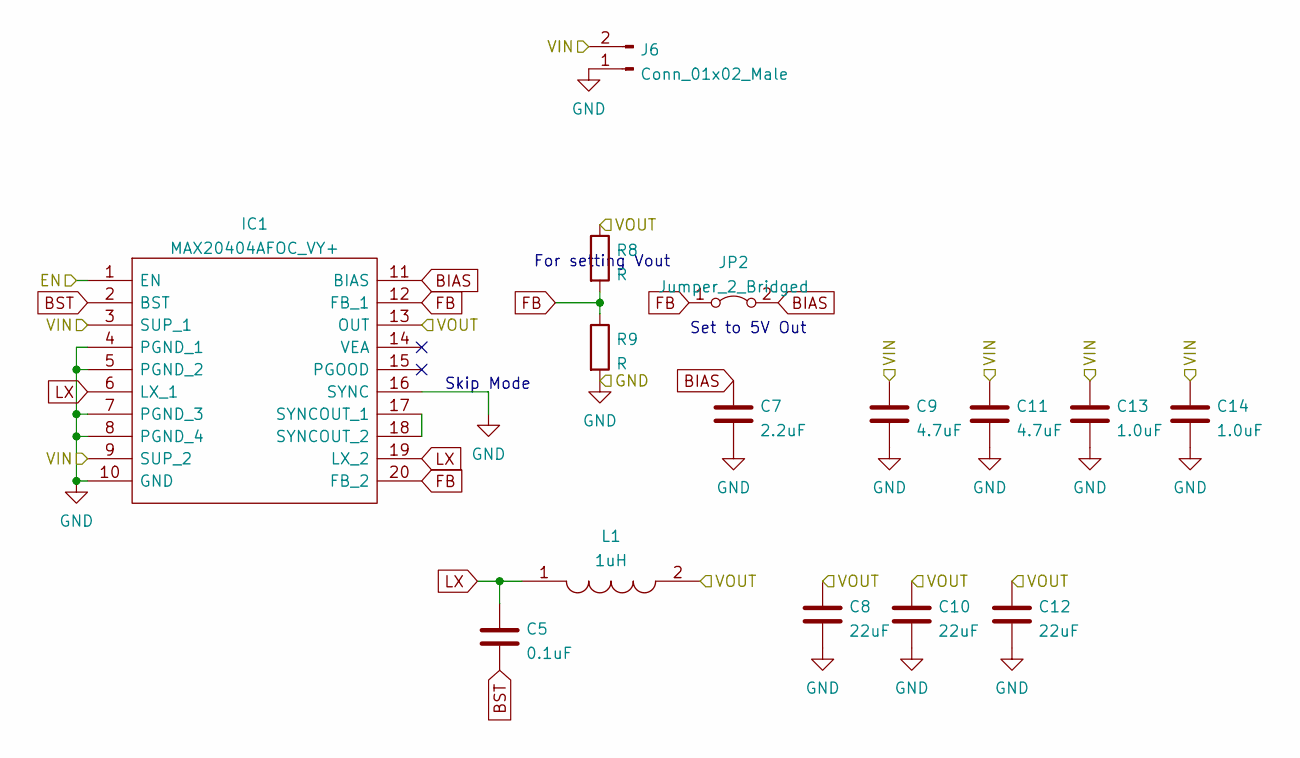
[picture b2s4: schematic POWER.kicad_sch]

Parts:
C5: 0.1uF; C_0805_2012Metric
C7: 2.2uF; C_0805_2012Metric
C8, C10, C12: 22uF; CP_Elec_5x5.3
C9, C11: 4.7uF; C_0805_2012Metric
C13, C14: 1.0uF; C_0805_2012Metric
IC1: MAX20404AFOC_VY+; MAX20404AFOCVY; Manufacturer_Part_Number MAX20404AFOC/VY+
J6: Conn_01x02_Male; AMASS_XT60-M_1x02_P7.20mm_Vertical
JP2: Jumper_2_Bridged; PinHeader_1x02_P2.54mm_Vertical
L1: 1uH; INDPM7066X500N; Manufacturer_Part_Number MWSA0605S-150MT
R8, R9: R; R_0805_2012Metric

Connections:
+5V: C8.1, C10.1, C12.1, IC1.13 (OUT), L1.2, R8.1; also elsewhere on the board
+BATT: C9.1, C11.1, C13.1, C14.1, IC1.1 (EN), IC1.3 (SUP_1), IC1.9 (SUP_2), J6.2; also elsewhere on the board
BIAS: C7.1, IC1.11 (BIAS), JP2.2 (B)
BST: C5.2, IC1.2 (BST)
FB: IC1.12 (FB_1), IC1.20 (FB_2), JP2.1 (A), R8.2, R9.1
GND: C7.2, C8.2, C9.2, C10.2, C11.2, C12.2, C13.2, C14.2, IC1.4 (PGND_1), IC1.5 (PGND_2), IC1.7 (PGND_3), IC1.8 (PGND_4), IC1.10 (GND), IC1.16 (SYNC), J6.1, R9.2; also elsewhere on the board
LX: C5.1, IC1.6 (LX_1), IC1.19 (LX_2), L1.1
unnamed: IC1.17 (SYNCOUT_1), IC1.18 (SYNCOUT_2)

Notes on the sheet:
For setting Vout
Skip Mode
Set to 5V Out
